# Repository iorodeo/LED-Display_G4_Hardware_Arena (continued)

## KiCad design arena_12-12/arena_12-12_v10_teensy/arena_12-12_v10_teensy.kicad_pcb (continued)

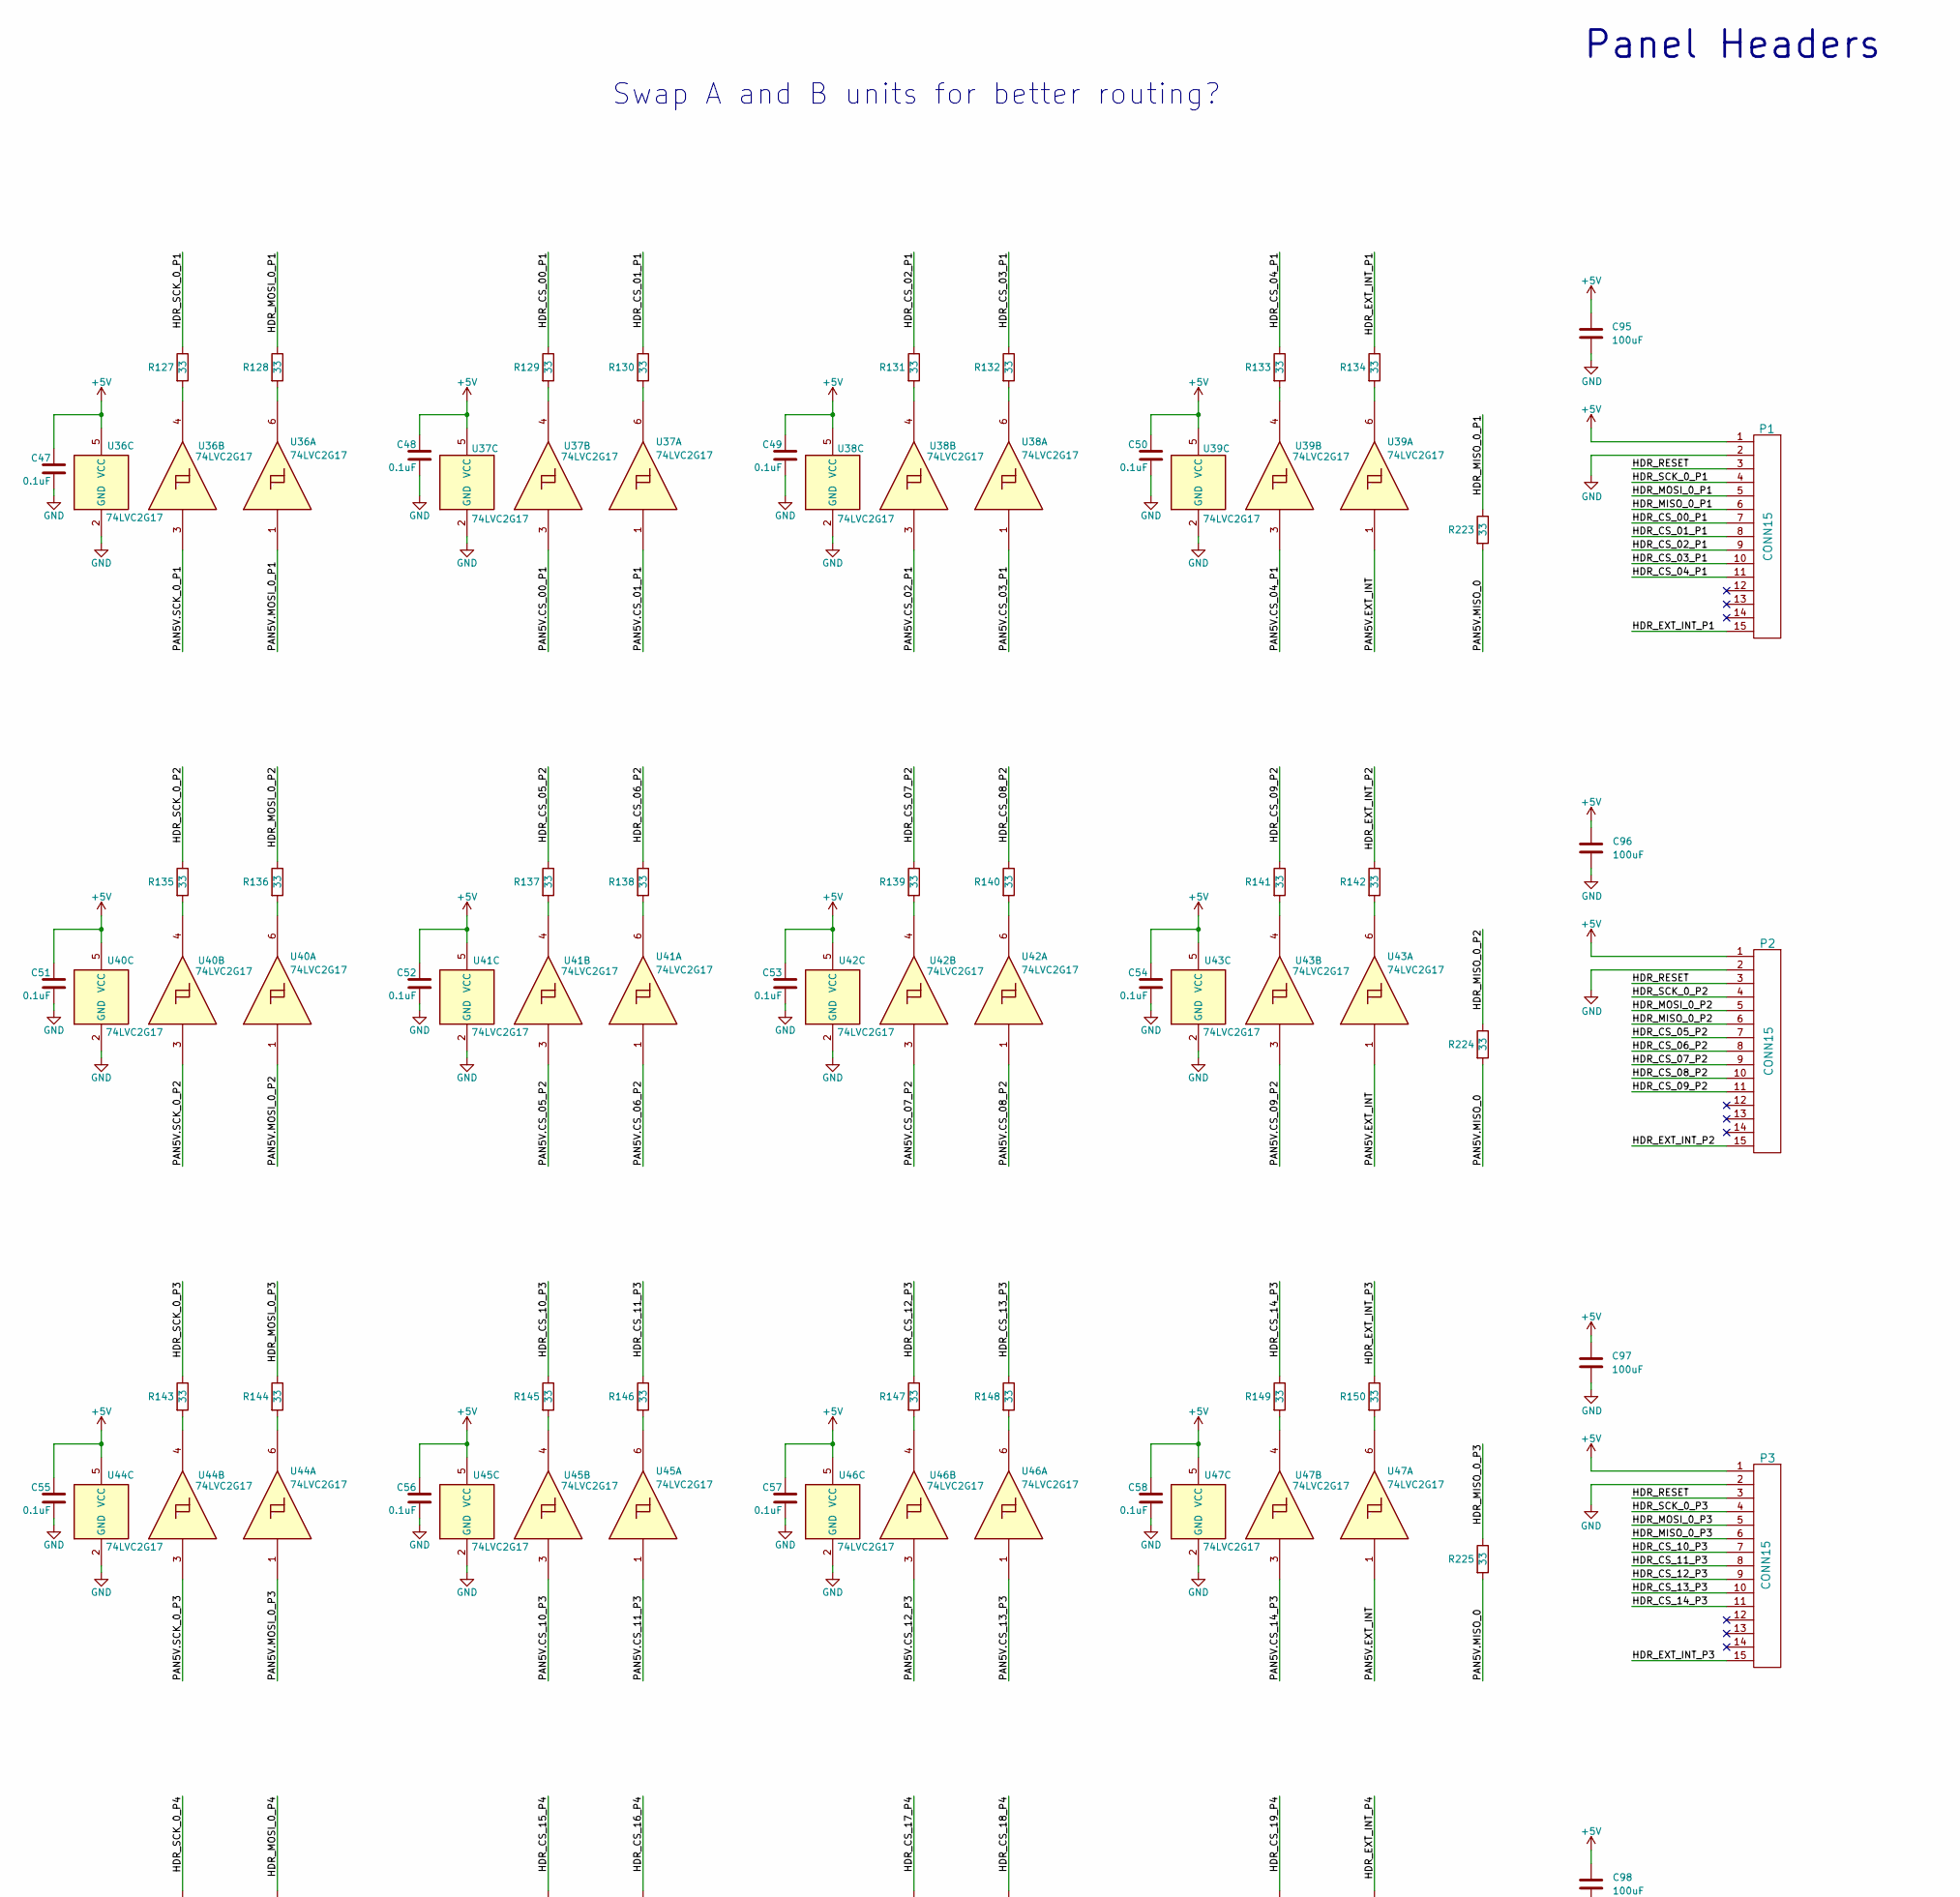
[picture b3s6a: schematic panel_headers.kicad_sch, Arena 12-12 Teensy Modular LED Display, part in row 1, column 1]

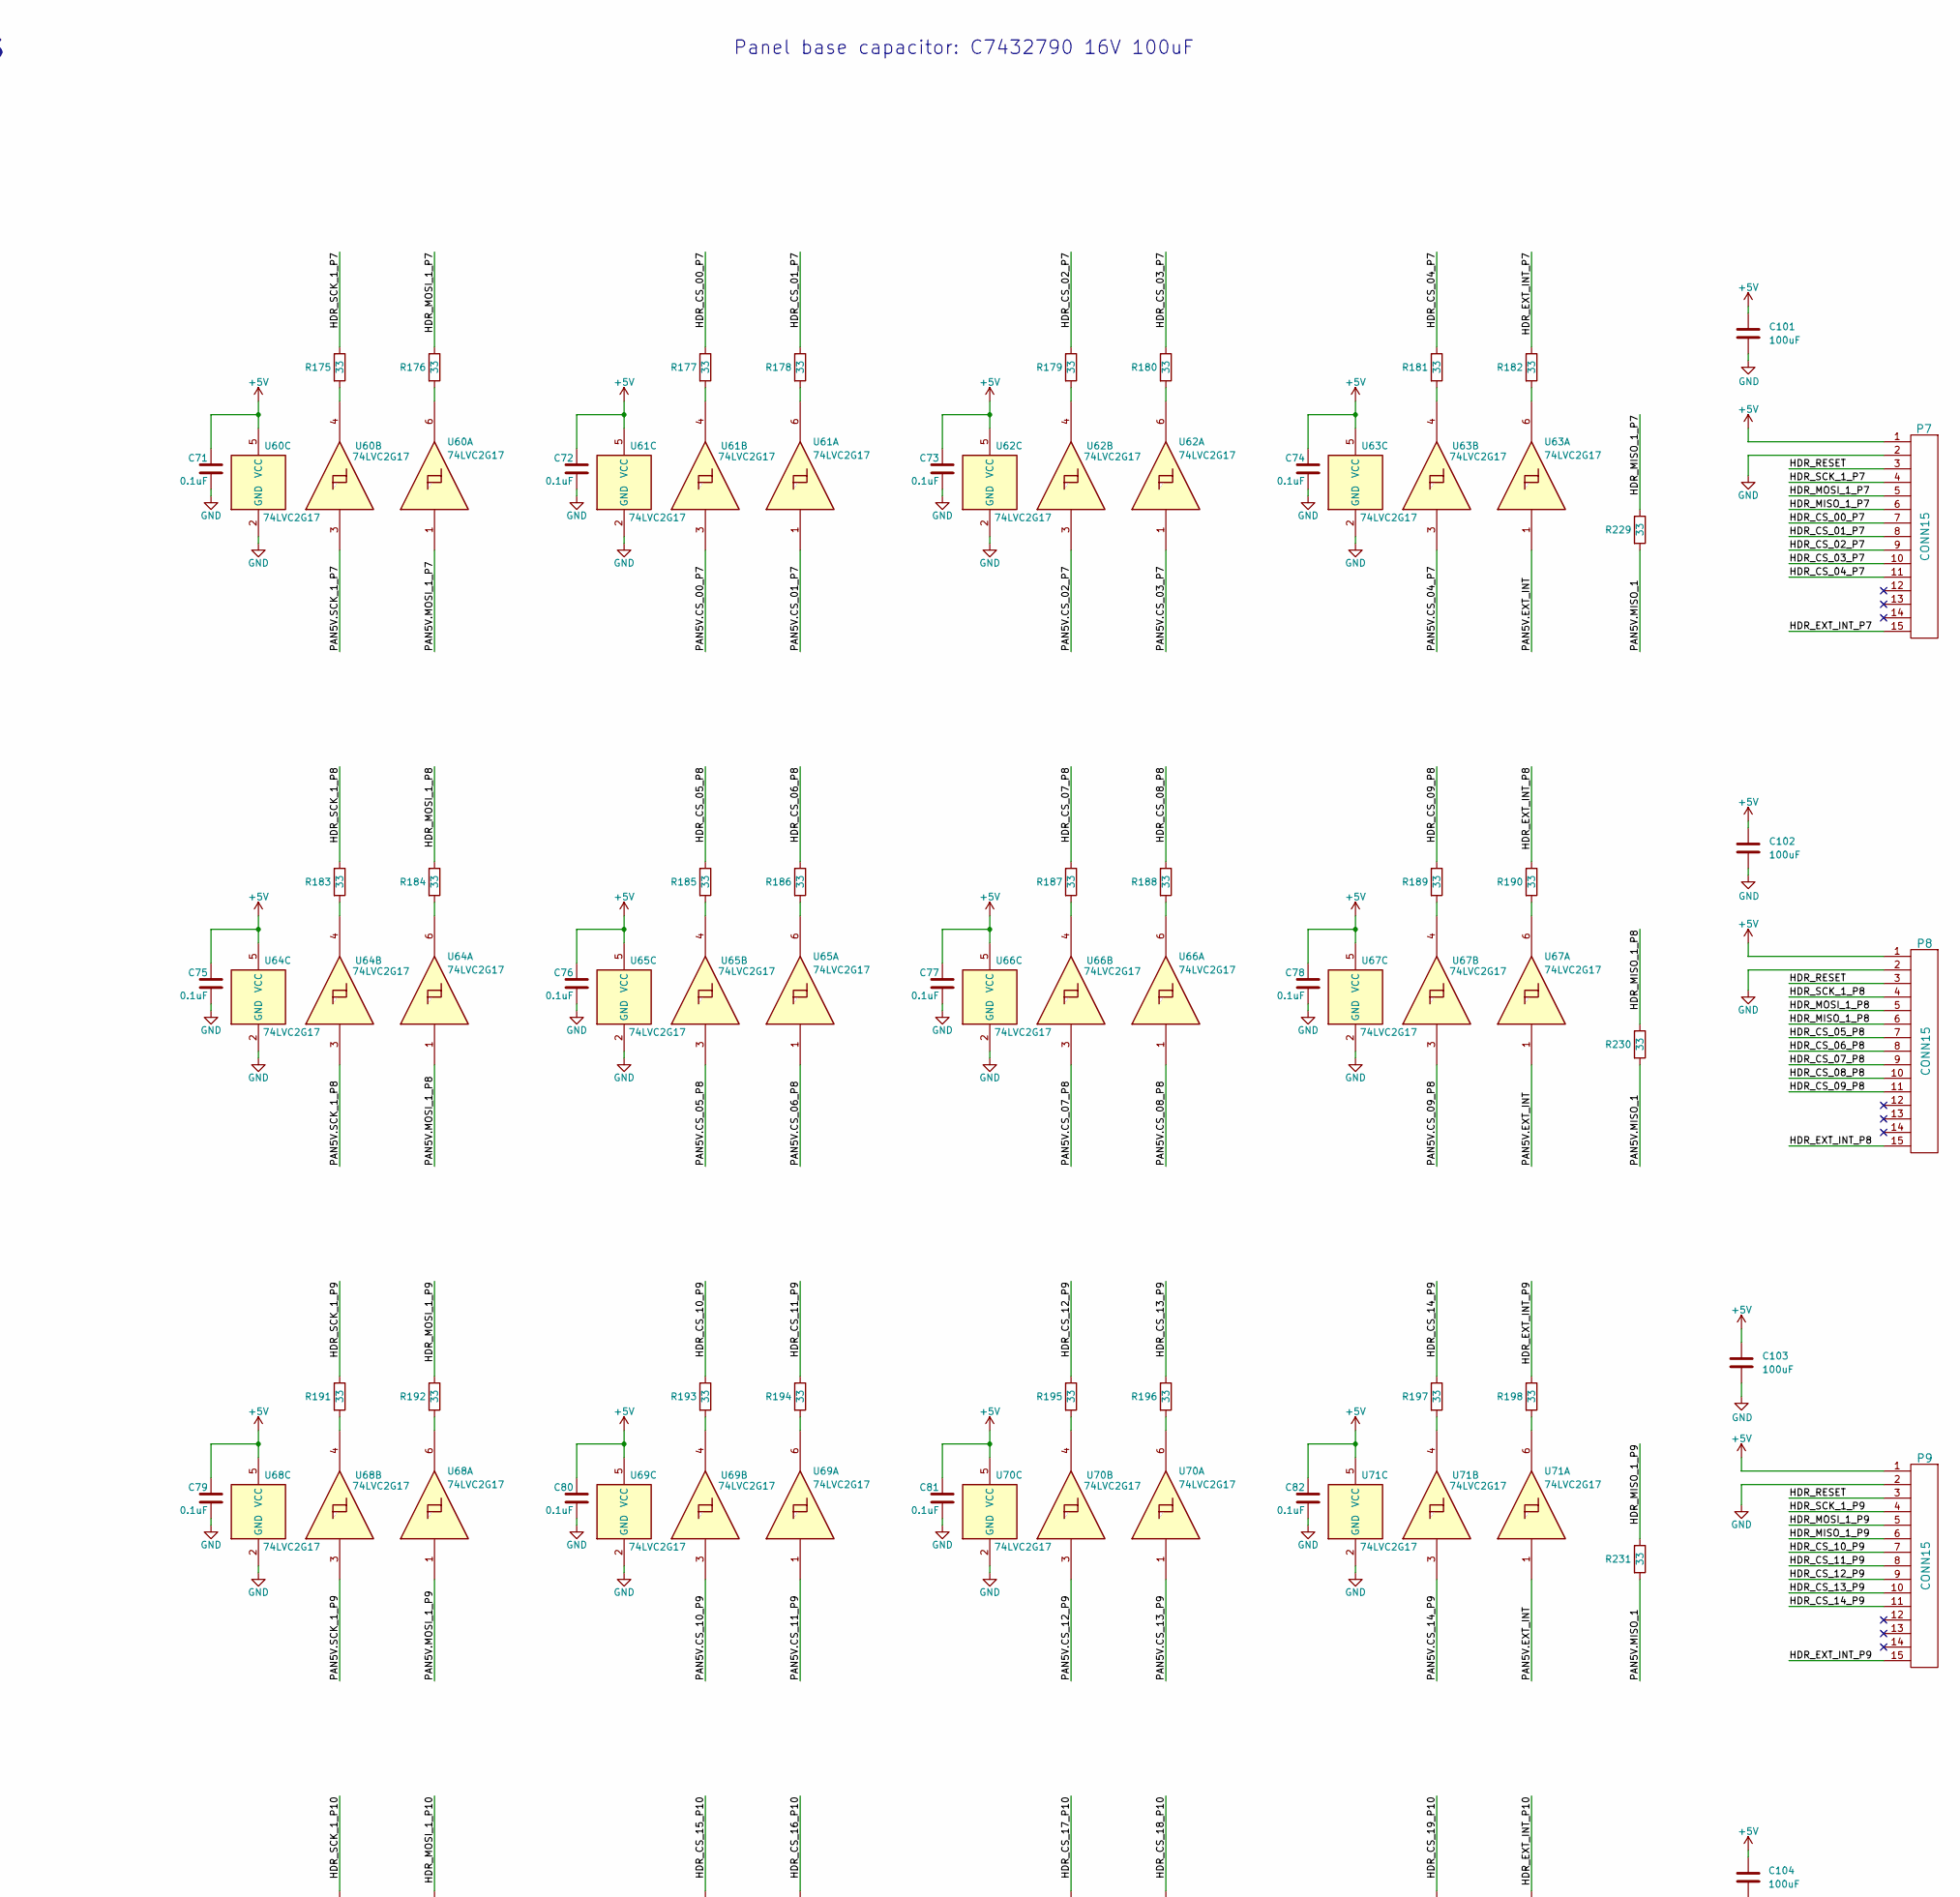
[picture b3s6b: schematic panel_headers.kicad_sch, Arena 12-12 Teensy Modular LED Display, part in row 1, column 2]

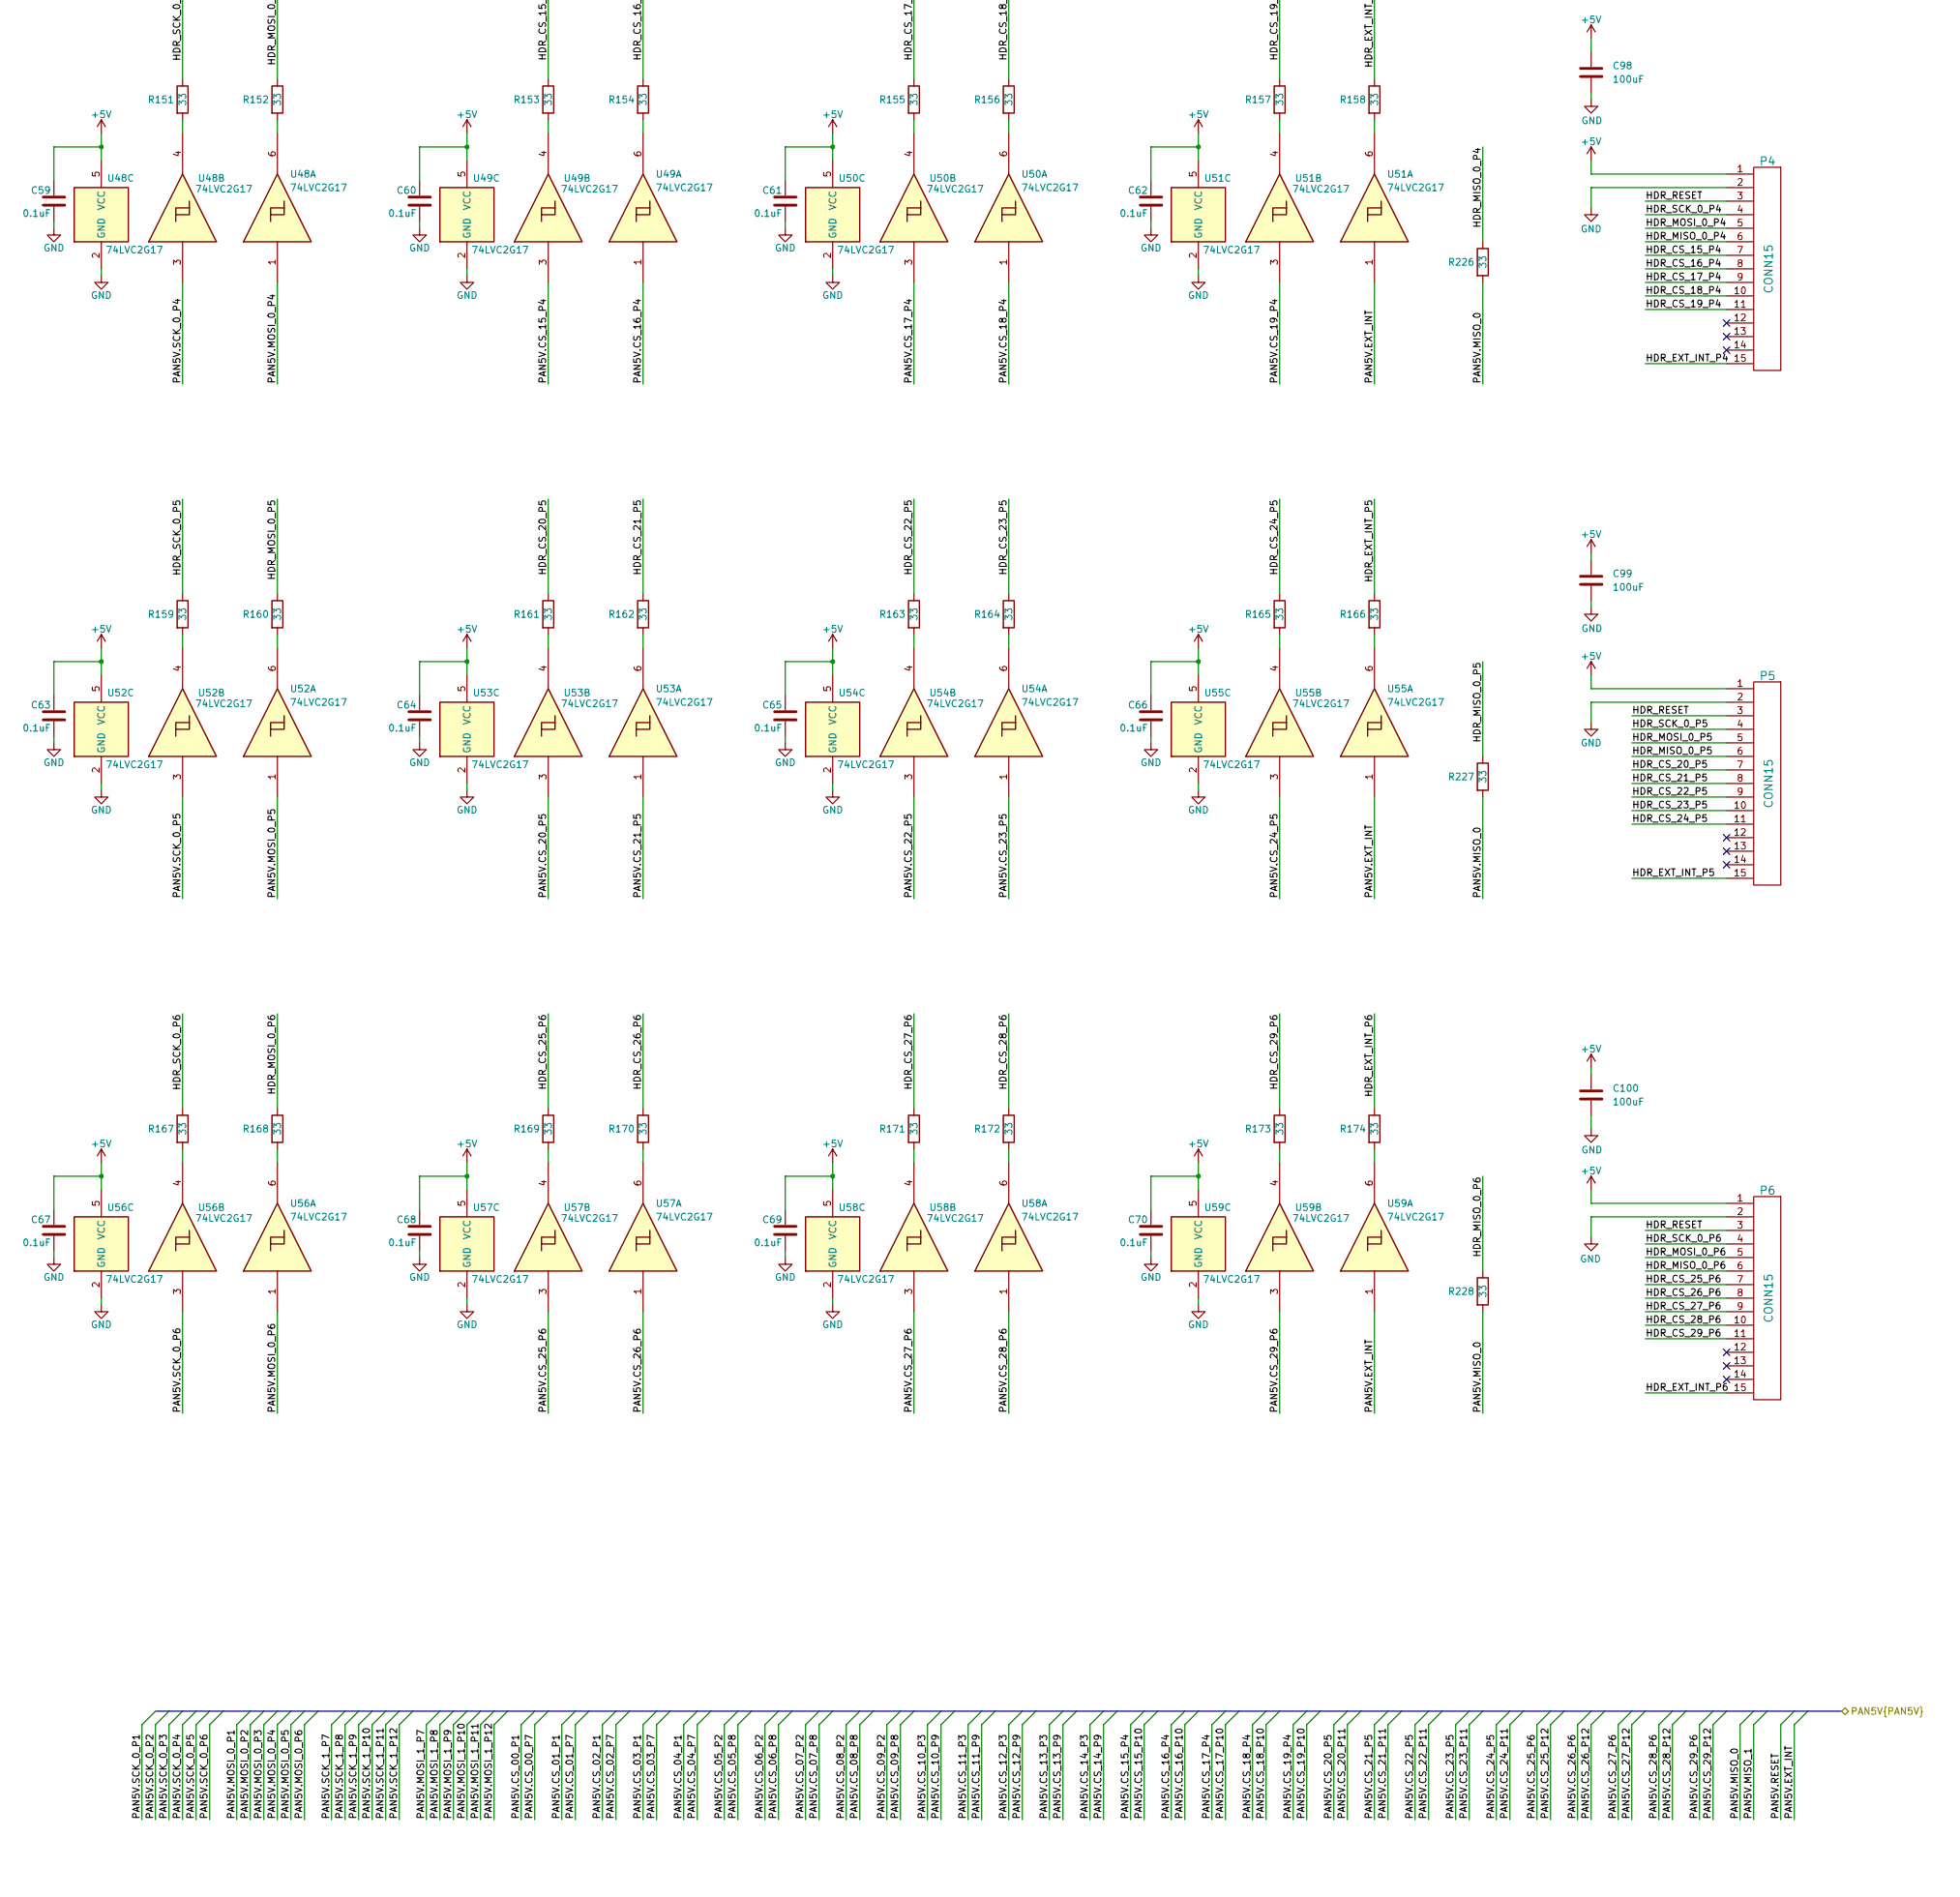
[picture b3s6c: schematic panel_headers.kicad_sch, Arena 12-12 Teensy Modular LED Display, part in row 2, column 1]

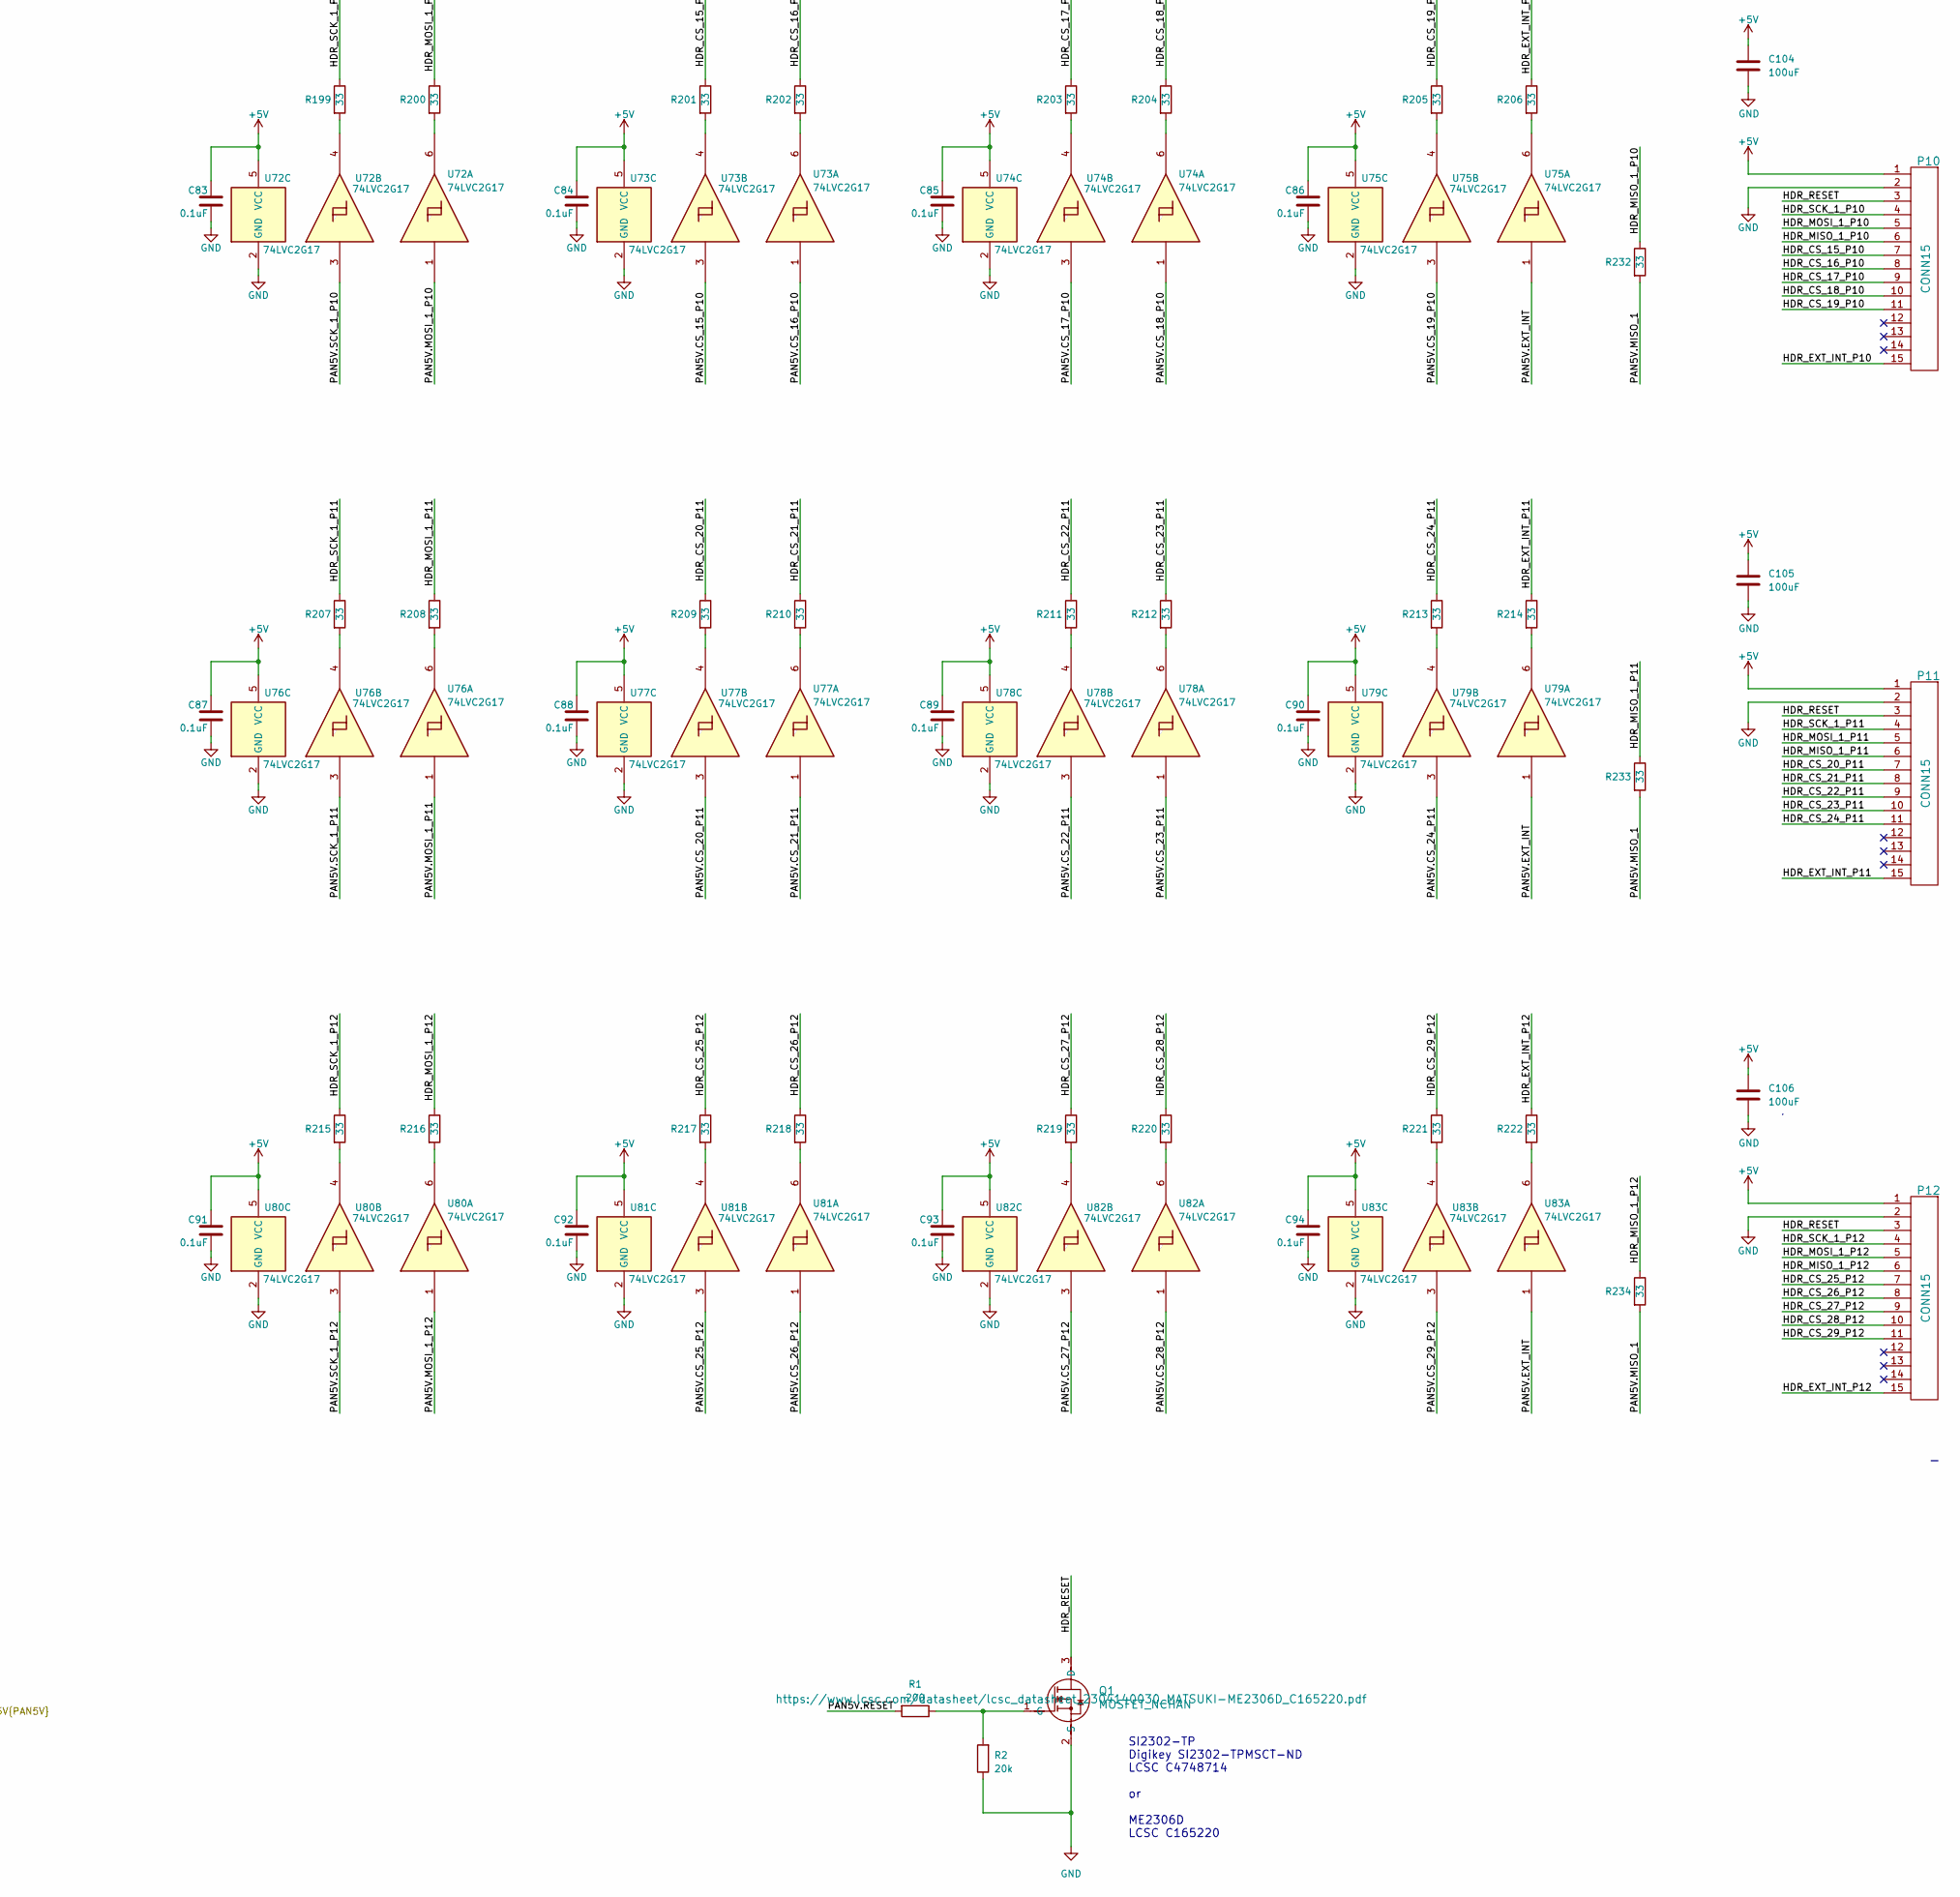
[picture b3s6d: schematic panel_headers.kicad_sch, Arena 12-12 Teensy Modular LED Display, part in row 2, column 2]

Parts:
C47, C48, C49, C50, C51, C52, C53, C54, C55, C56, C57, C58, C59, C60, C61, C62, C63, C64, C65, C66, C67, C68, C69, C70, C71, C72, C73, C74, C75, C76, C77, C78, C79, C80, C81, C82, C83, C84, C85, C86, C87, C88, C89, C90, C91, C92, C93, C94: 0.1uF; C_0402_1005Metric; MPN CL05B104KO5NNNC; DigiKey PN 1276-1001-2-ND
C95, C96, C97, C98, C99, C100, C101, C102, C103, C104, C105, C106: 100uF; C_1210_3225Metric; MPN HGC1210R5107M160NSVK; LCSC Part # C7432790
P1, P2, P3, P4, P5, P6, P7, P8, P9, P10, P11, P12: CONN15; HEADER_TOP; MPN PPPC151LFBN-RC; DigiKey PN S7048-ND
Q1: MOSFET_NCHAN; SOT-23-3; MPN ME2306D; LCSC Part # C165220
R1: 200; R_0402_1005Metric; MPN 0402WGF2000TCE; LCSC Part # C25087
R2: 20k; R_0402_1005Metric; MPN 0402WGF2002TCE; LCSC Part # C25765
R127, R128, R129, R130, R131, R132, R133, R134, R135, R136, R137, R138, R139, R140, R141, R142, R143, R144, R145, R146, R147, R148, R149, R150, R151, R152, R153, R154, R155, R156, R157, R158, R159, R160, R161, R162, R163, R164, R165, R166, R167, R168, R169, R170, R171, R172, R173, R174, R175, R176, R177, R178, R179, R180, R181, R182, R183, R184, R185, R186, R187, R188, R189, R190, R191, R192, R193, R194, R195, R196, R197, R198, R199, R200, R201, R202, R203, R204, R205, R206, R207, R208, R209, R210, R211, R212, R213, R214, R215, R216, R217, R218, R219, R220, R221, R222, R223, R224, R225, R226, R227, R228, R229, R230, R231, R232, R233, R234: 33; R_0402_1005Metric; MPN 0402WGF330JTCE; LCSC Part # C25105
U36, U37, U38, U39, U40, U41, U42, U43, U44, U45, U46, U47, U48, U49, U50, U51, U52, U53, U54, U55, U56, U57, U58, U59, U60, U61, U62, U63, U64, U65, U66, U67, U68, U69, U70, U71, U72, U73, U74, U75, U76, U77, U78, U79, U80, U81, U82, U83: 74LVC2G17; SOT-23-6; MPN SN74LVC2G17DBVR; DigiKey PN 296-SN74LVC2G17DBVRTR-ND

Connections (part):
+5V: C47.1, C48.1, C49.1, C50.1, C51.1, C52.1, C53.1, C54.1, C55.1, C56.1, C57.1, C58.1, C59.1, C60.1, C61.1, C62.1, C63.1, C64.1, C65.1, C66.1, C67.1, C68.1, C69.1, C70.1, C71.1, C72.1, C73.1, C74.1, C75.1, C76.1, C77.1, C78.1, C79.1, C80.1, C81.1, C82.1, C83.1, C84.1, C85.1, C86.1, C87.1, C88.1, C89.1, C90.1, C91.1, C92.1, C93.1, C94.1, C95.1, C96.1, C97.1, C98.1, C99.1, C100.1, C101.1, C102.1, C103.1, C104.1, C105.1, C106.1, P1.1, P2.1, P3.1, P4.1, P5.1, P6.1, P7.1, P8.1, P9.1, P10.1, P11.1, P12.1, U36.5 (VCC), U37.5 (VCC), U38.5 (VCC), U39.5 (VCC), U40.5 (VCC), U41.5 (VCC), U42.5 (VCC), U43.5 (VCC)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; also elsewhere on the board
/Level Shifters/PAN5V.CS_00_P1: U37.3; also elsewhere on the board
/Level Shifters/PAN5V.CS_00_P7: U61.3; also elsewhere on the board
/Level Shifters/PAN5V.CS_01_P1: U37.1; also elsewhere on the board
/Level Shifters/PAN5V.CS_01_P7: U61.1; also elsewhere on the board
/Level Shifters/PAN5V.CS_02_P1: U38.3; also elsewhere on the board
/Level Shifters/PAN5V.CS_02_P7: U62.3; also elsewhere on the board
/Level Shifters/PAN5V.CS_03_P1: U38.1; also elsewhere on the board
/Level Shifters/PAN5V.CS_03_P7: U62.1; also elsewhere on the board
/Level Shifters/PAN5V.CS_04_P1: U39.3; also elsewhere on the board
/Level Shifters/PAN5V.CS_04_P7: U63.3; also elsewhere on the board
/Level Shifters/PAN5V.CS_05_P2: U41.3; also elsewhere on the board
/Level Shifters/PAN5V.CS_05_P8: U65.3; also elsewhere on the board
/Level Shifters/PAN5V.CS_06_P2: U41.1; also elsewhere on the board
/Level Shifters/PAN5V.CS_06_P8: U65.1; also elsewhere on the board
/Level Shifters/PAN5V.CS_07_P2: U42.3; also elsewhere on the board
/Level Shifters/PAN5V.CS_07_P8: U66.3; also elsewhere on the board
/Level Shifters/PAN5V.CS_08_P2: U42.1; also elsewhere on the board
/Level Shifters/PAN5V.CS_08_P8: U66.1; also elsewhere on the board
/Level Shifters/PAN5V.CS_09_P2: U43.3; also elsewhere on the board
/Level Shifters/PAN5V.CS_09_P8: U67.3; also elsewhere on the board
/Level Shifters/PAN5V.CS_10_P3: U45.3; also elsewhere on the board
/Level Shifters/PAN5V.CS_10_P9: U69.3; also elsewhere on the board
/Level Shifters/PAN5V.CS_11_P3: U45.1; also elsewhere on the board
/Level Shifters/PAN5V.CS_11_P9: U69.1; also elsewhere on the board
/Level Shifters/PAN5V.CS_12_P3: U46.3; also elsewhere on the board
/Level Shifters/PAN5V.CS_12_P9: U70.3; also elsewhere on the board
/Level Shifters/PAN5V.CS_13_P3: U46.1; also elsewhere on the board
/Level Shifters/PAN5V.CS_13_P9: U70.1; also elsewhere on the board
/Level Shifters/PAN5V.CS_14_P3: U47.3; also elsewhere on the board
/Level Shifters/PAN5V.CS_14_P9: U71.3; also elsewhere on the board
/Level Shifters/PAN5V.CS_15_P4: U49.3; also elsewhere on the board
/Level Shifters/PAN5V.CS_15_P10: U73.3; also elsewhere on the board
/Level Shifters/PAN5V.CS_16_P4: U49.1; also elsewhere on the board
/Level Shifters/PAN5V.CS_16_P10: U73.1; also elsewhere on the board
/Level Shifters/PAN5V.CS_17_P4: U50.3; also elsewhere on the board
/Level Shifters/PAN5V.CS_17_P10: U74.3; also elsewhere on the board
/Level Shifters/PAN5V.CS_18_P4: U50.1; also elsewhere on the board
/Level Shifters/PAN5V.CS_18_P10: U74.1; also elsewhere on the board
/Level Shifters/PAN5V.CS_19_P4: U51.3; also elsewhere on the board
/Level Shifters/PAN5V.CS_19_P10: U75.3; also elsewhere on the board
/Level Shifters/PAN5V.CS_20_P5: U53.3; also elsewhere on the board
/Level Shifters/PAN5V.CS_20_P11: U77.3; also elsewhere on the board
/Level Shifters/PAN5V.CS_21_P5: U53.1; also elsewhere on the board
/Level Shifters/PAN5V.CS_21_P11: U77.1; also elsewhere on the board
/Level Shifters/PAN5V.CS_22_P5: U54.3; also elsewhere on the board
/Level Shifters/PAN5V.CS_22_P11: U78.3; also elsewhere on the board
/Level Shifters/PAN5V.CS_23_P5: U54.1; also elsewhere on the board
/Level Shifters/PAN5V.CS_23_P11: U78.1; also elsewhere on the board
/Level Shifters/PAN5V.CS_24_P5: U55.3; also elsewhere on the board
/Level Shifters/PAN5V.CS_24_P11: U79.3; also elsewhere on the board
/Level Shifters/PAN5V.CS_25_P6: U57.3; also elsewhere on the board
/Level Shifters/PAN5V.CS_25_P12: U81.3; also elsewhere on the board
/Level Shifters/PAN5V.CS_26_P6: U57.1; also elsewhere on the board
/Level Shifters/PAN5V.CS_26_P12: U81.1; also elsewhere on the board
/Level Shifters/PAN5V.CS_27_P6: U58.3; also elsewhere on the board
/Level Shifters/PAN5V.CS_27_P12: U82.3; also elsewhere on the board
/Level Shifters/PAN5V.CS_28_P6: U58.1; also elsewhere on the board
/Level Shifters/PAN5V.CS_28_P12: U82.1; also elsewhere on the board
/Level Shifters/PAN5V.CS_29_P6: U59.3; also elsewhere on the board
/Level Shifters/PAN5V.CS_29_P12: U83.3; also elsewhere on the board
/Level Shifters/PAN5V.EXT_INT: U39.1, U43.1, U47.1, U51.1, U55.1, U59.1, U63.1, U67.1, U71.1, U75.1, U79.1, U83.1; also elsewhere on the board
/Level Shifters/PAN5V.MISO_0: R223.2, R224.2, R225.2, R226.2, R227.2, R228.2; also elsewhere on the board
/Level Shifters/PAN5V.MISO_1: R229.2, R230.2, R231.2, R232.2, R233.2, R234.2; also elsewhere on the board
/Level Shifters/PAN5V.MOSI_0_P1: U36.1; also elsewhere on the board
/Level Shifters/PAN5V.MOSI_0_P2: U40.1; also elsewhere on the board
/Level Shifters/PAN5V.MOSI_0_P3: U44.1; also elsewhere on the board
/Level Shifters/PAN5V.MOSI_0_P4: U48.1; also elsewhere on the board
/Level Shifters/PAN5V.MOSI_0_P5: U52.1; also elsewhere on the board
/Level Shifters/PAN5V.MOSI_0_P6: U56.1; also elsewhere on the board
/Level Shifters/PAN5V.MOSI_1_P7: U60.1; also elsewhere on the board
/Level Shifters/PAN5V.MOSI_1_P8: U64.1; also elsewhere on the board
/Level Shifters/PAN5V.MOSI_1_P9: U68.1; also elsewhere on the board
/Level Shifters/PAN5V.MOSI_1_P10: U72.1; also elsewhere on the board
/Level Shifters/PAN5V.MOSI_1_P11: U76.1; also elsewhere on the board
/Level Shifters/PAN5V.MOSI_1_P12: U80.1; also elsewhere on the board
/Level Shifters/PAN5V.RESET: R1.2; also elsewhere on the board
/Level Shifters/PAN5V.SCK_0_P1: U36.3; also elsewhere on the board
/Level Shifters/PAN5V.SCK_0_P2: U40.3; also elsewhere on the board
/Level Shifters/PAN5V.SCK_0_P3: U44.3; also elsewhere on the board
/Level Shifters/PAN5V.SCK_0_P4: U48.3; also elsewhere on the board
/Level Shifters/PAN5V.SCK_0_P5: U52.3; also elsewhere on the board
/Level Shifters/PAN5V.SCK_0_P6: U56.3; also elsewhere on the board
/Level Shifters/PAN5V.SCK_1_P7: U60.3; also elsewhere on the board
/Level Shifters/PAN5V.SCK_1_P8: U64.3; also elsewhere on the board
/Level Shifters/PAN5V.SCK_1_P9: U68.3; also elsewhere on the board
/Level Shifters/PAN5V.SCK_1_P10: U72.3; also elsewhere on the board
/Level Shifters/PAN5V.SCK_1_P11: U76.3; also elsewhere on the board
/Level Shifters/PAN5V.SCK_1_P12: U80.3; also elsewhere on the board
/Panel Headers/HDR_CS_00_P1: P1.7, R129.1
/Panel Headers/HDR_CS_00_P7: P7.7, R177.1
/Panel Headers/HDR_CS_01_P1: P1.8, R130.1
/Panel Headers/HDR_CS_01_P7: P7.8, R178.1
/Panel Headers/HDR_CS_02_P1: P1.9, R131.1
/Panel Headers/HDR_CS_02_P7: P7.9, R179.1
/Panel Headers/HDR_CS_03_P1: P1.10, R132.1
/Panel Headers/HDR_CS_03_P7: P7.10, R180.1
/Panel Headers/HDR_CS_04_P1: P1.11, R133.1
/Panel Headers/HDR_CS_04_P7: P7.11, R181.1
/Panel Headers/HDR_CS_05_P2: P2.7, R137.1
/Panel Headers/HDR_CS_05_P8: P8.7, R185.1
/Panel Headers/HDR_CS_06_P2: P2.8, R138.1
/Panel Headers/HDR_CS_06_P8: P8.8, R186.1
/Panel Headers/HDR_CS_07_P2: P2.9, R139.1
/Panel Headers/HDR_CS_07_P8: P8.9, R187.1
/Panel Headers/HDR_CS_08_P2: P2.10, R140.1
/Panel Headers/HDR_CS_08_P8: P8.10, R188.1
/Panel Headers/HDR_CS_09_P2: P2.11, R141.1
/Panel Headers/HDR_CS_09_P8: P8.11, R189.1
/Panel Headers/HDR_CS_10_P3: P3.7, R145.1
/Panel Headers/HDR_CS_10_P9: P9.7, R193.1
/Panel Headers/HDR_CS_11_P3: P3.8, R146.1
/Panel Headers/HDR_CS_11_P9: P9.8, R194.1
/Panel Headers/HDR_CS_12_P3: P3.9, R147.1
/Panel Headers/HDR_CS_12_P9: P9.9, R195.1
/Panel Headers/HDR_CS_13_P3: P3.10, R148.1
/Panel Headers/HDR_CS_13_P9: P9.10, R196.1
/Panel Headers/HDR_CS_14_P3: P3.11, R149.1
/Panel Headers/HDR_CS_14_P9: P9.11, R197.1
/Panel Headers/HDR_CS_15_P4: P4.7, R153.1
/Panel Headers/HDR_CS_15_P10: P10.7, R201.1
/Panel Headers/HDR_CS_16_P4: P4.8, R154.1
/Panel Headers/HDR_CS_16_P10: P10.8, R202.1
/Panel Headers/HDR_CS_17_P4: P4.9, R155.1
/Panel Headers/HDR_CS_17_P10: P10.9, R203.1
/Panel Headers/HDR_CS_18_P4: P4.10, R156.1
/Panel Headers/HDR_CS_18_P10: P10.10, R204.1
/Panel Headers/HDR_CS_19_P4: P4.11, R157.1
/Panel Headers/HDR_CS_19_P10: P10.11, R205.1
/Panel Headers/HDR_CS_20_P5: P5.7, R161.1
/Panel Headers/HDR_CS_20_P11: P11.7, R209.1
/Panel Headers/HDR_CS_21_P5: P5.8, R162.1
/Panel Headers/HDR_CS_21_P11: P11.8, R210.1
/Panel Headers/HDR_CS_22_P5: P5.9, R163.1
/Panel Headers/HDR_CS_22_P11: P11.9, R211.1
/Panel Headers/HDR_CS_23_P5: P5.10, R164.1
/Panel Headers/HDR_CS_23_P11: P11.10, R212.1
/Panel Headers/HDR_CS_24_P5: P5.11, R165.1
/Panel Headers/HDR_CS_24_P11: P11.11, R213.1
/Panel Headers/HDR_CS_25_P6: P6.7, R169.1
/Panel Headers/HDR_CS_25_P12: P12.7, R217.1
/Panel Headers/HDR_CS_26_P6: P6.8, R170.1
/Panel Headers/HDR_CS_26_P12: P12.8, R218.1
/Panel Headers/HDR_CS_27_P6: P6.9, R171.1
/Panel Headers/HDR_CS_27_P12: P12.9, R219.1
/Panel Headers/HDR_CS_28_P6: P6.10, R172.1
/Panel Headers/HDR_CS_28_P12: P12.10, R220.1
/Panel Headers/HDR_CS_29_P6: P6.11, R173.1
/Panel Headers/HDR_CS_29_P12: P12.11, R221.1
/Panel Headers/HDR_EXT_INT_P1: P1.15, R134.1
/Panel Headers/HDR_EXT_INT_P2: P2.15, R142.1
/Panel Headers/HDR_EXT_INT_P3: P3.15, R150.1
/Panel Headers/HDR_EXT_INT_P4: P4.15, R158.1
/Panel Headers/HDR_EXT_INT_P5: P5.15, R166.1
/Panel Headers/HDR_EXT_INT_P6: P6.15, R174.1
/Panel Headers/HDR_EXT_INT_P7: P7.15, R182.1
/Panel Headers/HDR_EXT_INT_P8: P8.15, R190.1
/Panel Headers/HDR_EXT_INT_P9: P9.15, R198.1
/Panel Headers/HDR_EXT_INT_P10: P10.15, R206.1
/Panel Headers/HDR_EXT_INT_P11: P11.15, R214.1
/Panel Headers/HDR_EXT_INT_P12: P12.15, R222.1
/Panel Headers/HDR_MISO_0_P1: P1.6, R223.1
/Panel Headers/HDR_MISO_0_P2: P2.6, R224.1
/Panel Headers/HDR_MISO_0_P3: P3.6, R225.1
/Panel Headers/HDR_MISO_0_P4: P4.6, R226.1
/Panel Headers/HDR_MISO_0_P5: P5.6, R227.1
/Panel Headers/HDR_MISO_0_P6: P6.6, R228.1
/Panel Headers/HDR_MISO_1_P7: P7.6, R229.1
/Panel Headers/HDR_MISO_1_P8: P8.6, R230.1
/Panel Headers/HDR_MISO_1_P9: P9.6, R231.1
/Panel Headers/HDR_MISO_1_P10: P10.6, R232.1
/Panel Headers/HDR_MISO_1_P11: P11.6, R233.1
/Panel Headers/HDR_MISO_1_P12: P12.6, R234.1
/Panel Headers/HDR_MOSI_0_P1: P1.5, R128.1
/Panel Headers/HDR_MOSI_0_P2: P2.5, R136.1
/Panel Headers/HDR_MOSI_0_P3: P3.5, R144.1
/Panel Headers/HDR_MOSI_0_P4: P4.5, R152.1
/Panel Headers/HDR_MOSI_0_P5: P5.5, R160.1
/Panel Headers/HDR_MOSI_0_P6: P6.5, R168.1
/Panel Headers/HDR_MOSI_1_P7: P7.5, R176.1
/Panel Headers/HDR_MOSI_1_P8: P8.5, R184.1
/Panel Headers/HDR_MOSI_1_P9: P9.5, R192.1
/Panel Headers/HDR_MOSI_1_P10: P10.5, R200.1
/Panel Headers/HDR_MOSI_1_P11: P11.5, R208.1
/Panel Headers/HDR_MOSI_1_P12: P12.5, R216.1
/Panel Headers/HDR_RESET: P1.3, P2.3, P3.3, P4.3, P5.3, P6.3, P7.3, P8.3, P9.3, P10.3, P11.3, P12.3, Q1.3 (D)
/Panel Headers/HDR_SCK_0_P1: P1.4, R127.1
/Panel Headers/HDR_SCK_0_P2: P2.4, R135.1
/Panel Headers/HDR_SCK_0_P3: P3.4, R143.1
/Panel Headers/HDR_SCK_0_P4: P4.4, R151.1
/Panel Headers/HDR_SCK_0_P5: P5.4, R159.1
/Panel Headers/HDR_SCK_0_P6: P6.4, R167.1
/Panel Headers/HDR_SCK_1_P7: P7.4, R175.1
/Panel Headers/HDR_SCK_1_P8: P8.4, R183.1
/Panel Headers/HDR_SCK_1_P9: P9.4, R191.1
/Panel Headers/HDR_SCK_1_P10: P10.4, R199.1
/Panel Headers/HDR_SCK_1_P11: P11.4, R207.1
/Panel Headers/HDR_SCK_1_P12: P12.4, R215.1
GND: C47.2, C48.2, C49.2, C50.2, C51.2, C52.2, C53.2, C54.2, C55.2, C56.2, C57.2, C58.2, C59.2, C60.2, C61.2, C62.2, C63.2, C64.2, C65.2, C66.2, C67.2, C68.2, C69.2, C70.2, C71.2, C72.2, C73.2, C74.2, C75.2, C76.2, C77.2, C78.2, C79.2, C80.2, C81.2, C82.2, C83.2, C84.2, C85.2, C86.2, C87.2, C88.2, C89.2, C90.2, C91.2, C92.2, C93.2, C94.2, C95.2, C96.2, C97.2, C98.2, C99.2, C100.2, C101.2, C102.2, C103.2, C104.2, C105.2, C106.2, P1.2, P2.2, P3.2, P4.2, P5.2, P6.2, P7.2, P8.2, P9.2, P10.2, P11.2, P12.2, Q1.2 (S), R2.1, U36.2 (GND), U37.2 (GND), U38.2 (GND), U39.2 (GND), U40.2 (GND), U41.2 (GND)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; also elsewhere on the board
unnamed: Q1.1 (G), R1.1, R2.2
unnamed: R127.2, U36.4
unnamed: R128.2, U36.6
unnamed: R129.2, U37.4
unnamed: R130.2, U37.6
unnamed: R131.2, U38.4
unnamed: R132.2, U38.6
unnamed: R133.2, U39.4
unnamed: R134.2, U39.6
unnamed: R135.2, U40.4
unnamed: R136.2, U40.6
unnamed: R137.2, U41.4
unnamed: R138.2, U41.6
unnamed: R139.2, U42.4
unnamed: R140.2, U42.6
unnamed: R141.2, U43.4
unnamed: R142.2, U43.6
unnamed: R143.2, U44.4
unnamed: R144.2, U44.6
unnamed: R145.2, U45.4
unnamed: R146.2, U45.6
unnamed: R147.2, U46.4
unnamed: R148.2, U46.6
unnamed: R149.2, U47.4
unnamed: R150.2, U47.6
unnamed: R151.2, U48.4
unnamed: R152.2, U48.6
unnamed: R153.2, U49.4
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
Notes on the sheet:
Panel base capacitor: C7432790 16V 100uF
Panel Headers
Swap A and B units for better routing?
SI2302-TP Digikey SI2302-TPMSCT-ND LCSC C4748714 or ME2306D LCSC C165220
